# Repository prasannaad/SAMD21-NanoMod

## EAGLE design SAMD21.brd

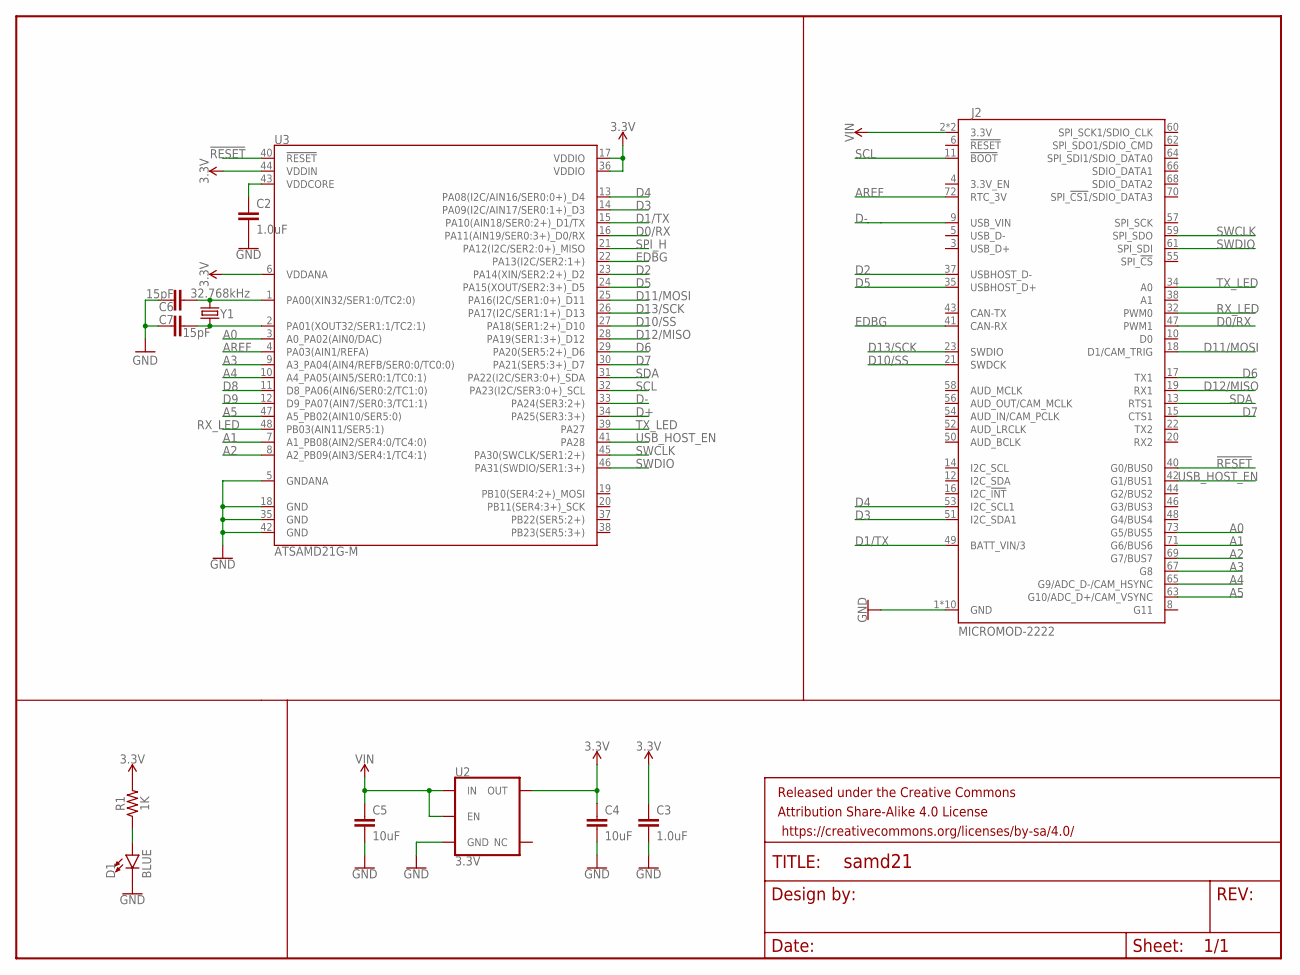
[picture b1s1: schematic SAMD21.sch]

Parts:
C2, C3: 1.0uF; 0603
C4, C5: 10uF; 0603
C6, C7: 15pF; 0402-CAP
D1: BLUE; LED-0603
FRAME1: FRAME-LETTER; CREATIVE_COMMONS
J2: MICROMOD-2222; M.2-CARD-E-22
R1: 1K; 0603
U2: 3.3V; SOT23-5
U3: ATSAMD21G-M; QFN-48
Y1: 32.768kHz; CRYSTAL-SMD-3.2X1.5MM

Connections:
3.3V: C3.1, C4.1, R1.2, U2.5 (OUT), U3.6 (VDDANA), U3.17 (VDDIO), U3.36 (VDDIO), U3.44 (VDDIN)
!RESET: J2.40 (G0/BUS0), U3.40 (!RESET!)
A0: J2.73 (G5/BUS5), U3.3 (A0_PA02(AIN0/DAC))
A1: J2.71 (G6/BUS6), U3.7 (A1_PB08(AIN2/SER4:0/TC4:0))
A2: J2.69 (G7/BUS7), U3.8 (A2_PB09(AIN3/SER4:1/TC4:1))
A3: J2.67 (G8), U3.9 (A3_PA04(AIN4/REFB/SER0:0/TC0:0))
A4: J2.65 (G9/ADC_D-/CAM_HSYNC), U3.10 (A4_PA05(AIN5/SER0:1/TC0:1))
A5: J2.63 (G10/ADC_D+/CAM_VSYNC), U3.47 (A5_PB02(AIN10/SER5:0))
AREF: J2.72 (RTC_3V), U3.4 (PA03(AIN1/REFA))
D0/RX: J2.47 (PWM1), U3.16 (PA11(AIN19/SER0:3+)_D0/RX)
D1/TX: J2.49 (BATT_VIN/3), U3.15 (PA10(AIN18/SER0:2+)_D1/TX)
D2: J2.37 (USBHOST_D-), U3.23 (PA14(XIN/SER2:2+)_D2)
D3: J2.51 (I2C_SDA1), U3.14 (PA09(I2C/AIN17/SER0:1+)_D3)
D4: J2.53 (I2C_SCL1), U3.13 (PA08(I2C/AIN16/SER0:0+)_D4)
D5: J2.35 (USBHOST_D+), U3.24 (PA15(XOUT/SER2:3+)_D5)
D6: J2.17 (TX1), U3.29 (PA20(SER5:2+)_D6)
D7: J2.15 (CTS1), U3.30 (PA21(SER5:3+)_D7)
D8: U3.11 (D8_PA06(AIN6/SER0:2/TC1:0))
D9: U3.12 (D9_PA07(AIN7/SER0:3/TC1:1))
D10/SS: J2.21 (SWDCK), U3.27 (PA18(SER1:2+)_D10)
D11/MOSI: J2.18 (D1/CAM_TRIG), U3.25 (PA16(I2C/SER1:0+)_D11)
D12/MISO: J2.19 (RX1), U3.28 (PA19(SER1:3+)_D12)
D13/SCK: J2.23 (SWDIO), U3.26 (PA17(I2C/SER1:1+)_D13)
D+: U3.34 (PA25(SER3:3+))
D-: J2.9 (USB_VIN), U3.33 (PA24(SER3:2+))
EDBG: J2.41 (CAN-RX), U3.22 (PA13(I2C/SER2:1+))
GND: C2.2, C3.2, C4.2, C5.2, C6.1, C7.2, D1.C, J2.1 (GND), J2.7 (GND), J2.33 (GND), J2.36 (GND), J2.39 (GND), J2.45 (GND), J2.75 (GND), J2.GND1 (GND), J2.GND2 (GND), J2.GND3 (GND), U2.2 (GND), U3.5 (GNDANA), U3.18 (GND), U3.35 (GND), U3.42 (GND)
unnamed: D1.A, R1.1
unnamed: C6.2, U3.1 (PA00(XIN32/SER1:0/TC2:0)), Y1.P$2 (2)
unnamed: C7.1, U3.2 (PA01(XOUT32/SER1:1/TC2:1)), Y1.P$1 (1)
unnamed: C2.1, U3.43 (VDDCORE)
RX_LED: J2.32 (PWM0), U3.48 (PB03(AIN11/SER5:1))
SCL: J2.11 (!BOOT!), U3.32 (PA23(I2C/SER3:0+)_SCL)
SDA: J2.13 (RTS1), U3.31 (PA22(I2C/SER3:0+)_SDA)
SPI_H: U3.21 (PA12(I2C/SER2:0+)_MISO)
SWCLK: J2.59 (SPI_SDO), U3.45 (PA30(SWCLK/SER1:2+))
SWDIO: J2.61 (SPI_SDI), U3.46 (PA31(SWDIO/SER1:3+))
TX_LED: J2.34 (A0), U3.39 (PA27)
USB_HOST_EN: J2.42 (G1/BUS1), U3.41 (PA28)
VIN: C5.1, J2.2 (3.3V), J2.74 (3.3V), U2.1 (IN), U2.3 (EN)

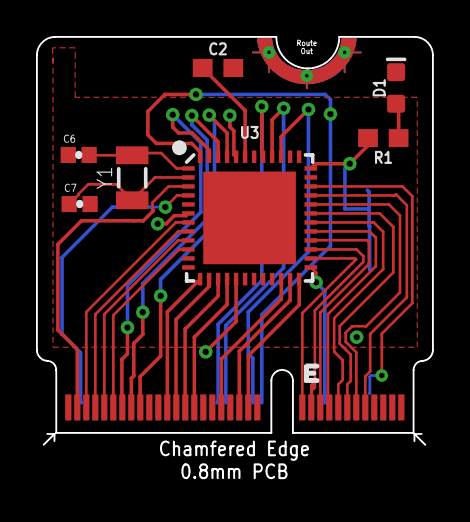
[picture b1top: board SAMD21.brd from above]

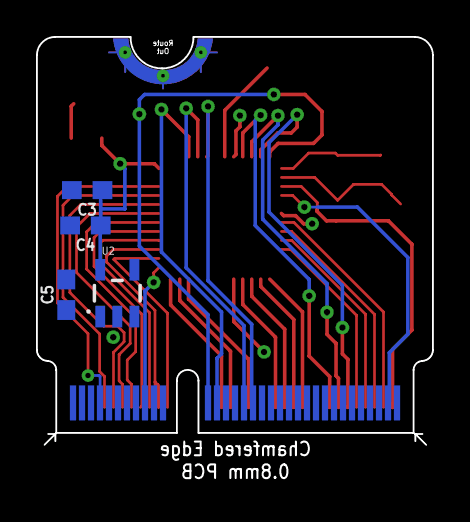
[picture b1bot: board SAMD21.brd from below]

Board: 4 copper layers, 22.0 x 24.9 mm, 13 parts (4 on the bottom side), 36 nets.

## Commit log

2020-10-24 Create LISCENCE
2020-10-24 Create LICENSE

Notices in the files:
parts and their libraries:
SparkFun-Aesthetics: Licensing: Creative Commons ShareAlike 4.0 International - https://creativecommons.org/licenses/by-sa/4.0
SparkFun-Aesthetics: Released under the Creative Commons Attribution Share-Alike 4.0 License
SparkFun-Aesthetics: https://creativecommons.org/licenses/by-sa/4.0
